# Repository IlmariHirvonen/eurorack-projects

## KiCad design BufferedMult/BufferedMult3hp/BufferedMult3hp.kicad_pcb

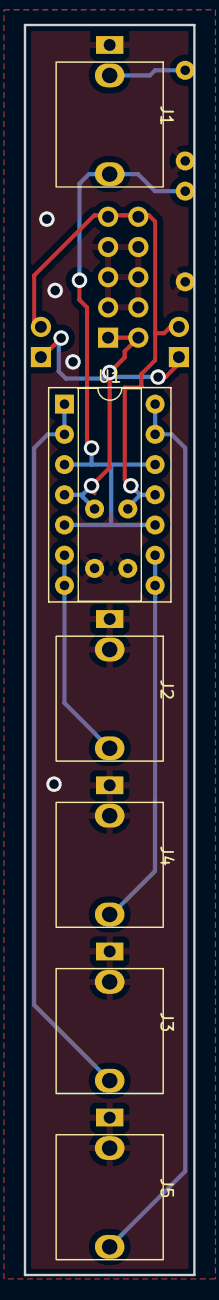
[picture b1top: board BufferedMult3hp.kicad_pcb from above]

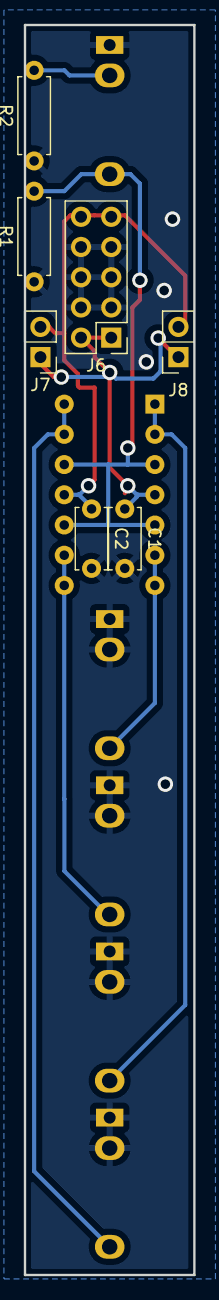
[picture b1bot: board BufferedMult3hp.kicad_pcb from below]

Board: 2 copper layers, 14.2 x 105.1 mm, 13 parts (7 on the bottom side), 9 nets.

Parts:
C1, C2: 100n; C_Disc_D5.0mm_W2.5mm_P5.00mm
J1, J2, J3, J4, J5: AudioJack2_SwitchT; Thonkiconn
J6: Conn_02x05_Odd_Even; PinHeader_2x05_P2.54mm_Vertical
J7: Conn_01x02_Male; PinHeader_1x02_P2.54mm_Vertical
J8: Conn_01x02_Female; PinSocket_1x02_P2.54mm_Vertical
R1: 1Meg; R_Axial_DIN0207_L6.3mm_D2.5mm_P7.62mm_Horizontal
R2: 20k; R_Axial_DIN0207_L6.3mm_D2.5mm_P7.62mm_Horizontal
U1: LM324; DIP-14_W7.62mm_Socket

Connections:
+12V: C1.1, J6.1, J6.2, J7.1, J8.1, U1.4 (V+)
-12V: C2.1, J6.9, J6.10, J7.2, J8.2, U1.11 (V-)
GND: C1.2, C2.2, J1.S, J2.S, J2.TN, J3.S, J3.TN, J4.S, J4.TN, J5.S, J5.TN, J6.3, J6.4, J6.5, J6.6, J6.7, J6.8, R1.1, R2.1
unnamed: J1.TN, R2.2
unnamed: J4.T, U1.8, U1.9 (-)
unnamed: J3.T, U1.1, U1.2 (-)
unnamed: J2.T, U1.6 (-), U1.7
unnamed: J1.T, R1.2, U1.3 (+), U1.5 (+), U1.10 (+), U1.12 (+)
unnamed: J5.T, U1.13 (-), U1.14

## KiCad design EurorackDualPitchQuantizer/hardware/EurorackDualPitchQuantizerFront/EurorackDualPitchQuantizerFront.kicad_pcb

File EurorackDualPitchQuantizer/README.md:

# EurorackDualPitchQuantizer
A simple Arduino and MCP4725 DAC based pitch quantizer. It might not be the best designed module or it might not work at all yet. I have yet to assemble a working unit or program the non test firmware for the microcontroller. I'll update this as the project goes along.

### Licenses
The license for hardware is under the hardware folder and for software under software folder. But in short:
Software: GPL3.0.
Hardware: CERN-OHL-S v2

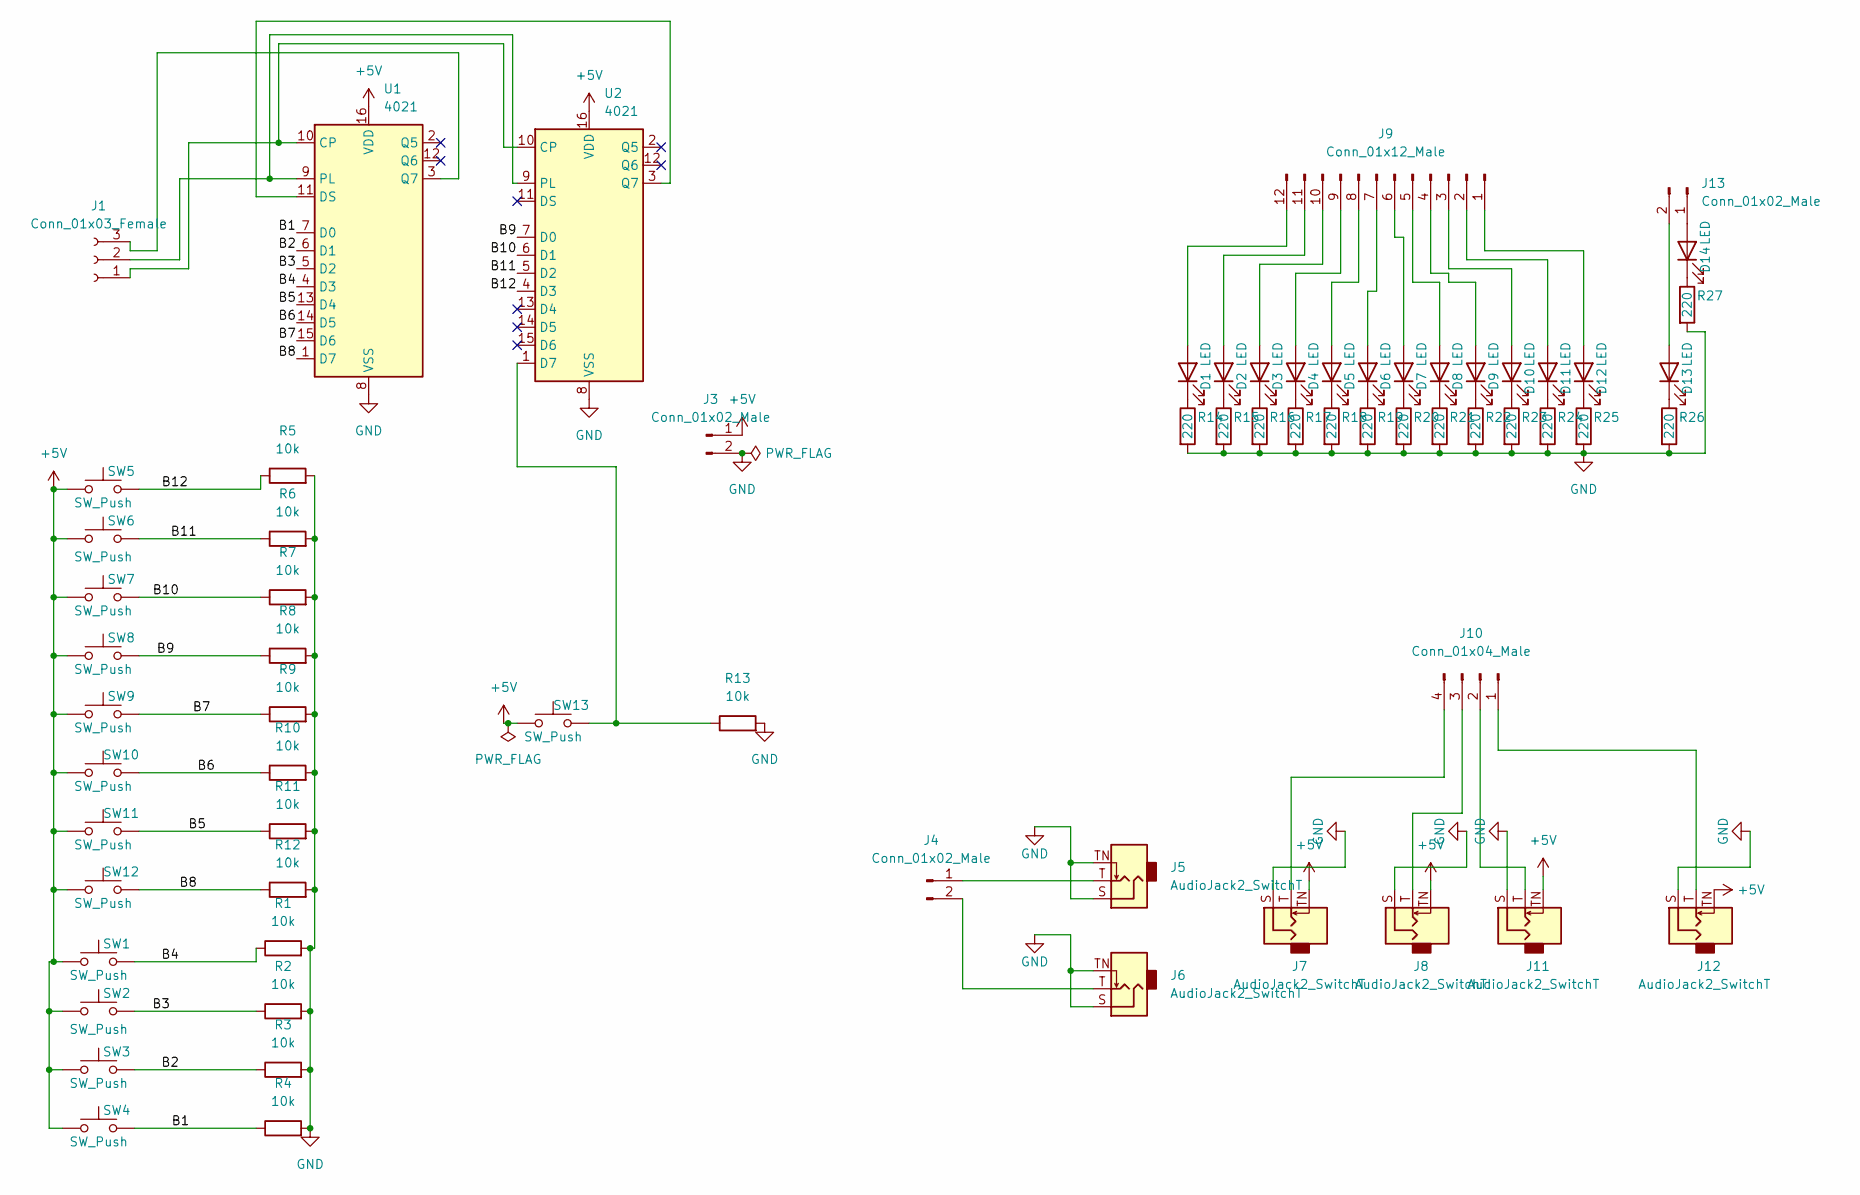
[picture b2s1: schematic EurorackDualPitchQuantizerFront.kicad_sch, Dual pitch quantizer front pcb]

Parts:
D1, D2, D3, D4, D5, D6, D7, D8, D9, D10, D11, D12, D13, D14: LED; LED_D3.0mm
J1: Conn_01x03_Female; PinHeader_1x03_P2.54mm_Vertical
J3, J4, J13: Conn_01x02_Male; PinHeader_1x02_P2.54mm_Vertical
J5, J6, J7, J8, J11, J12: AudioJack2_SwitchT; Thonkiconn
J9: Conn_01x12_Male; PinHeader_1x12_P2.54mm_Vertical
J10: Conn_01x04_Male; PinHeader_1x04_P2.54mm_Vertical
R1, R2, R3, R4, R5, R6, R7, R8, R9, R10, R11, R12, R13: 10k; R_Axial_DIN0207_L6.3mm_D2.5mm_P7.62mm_Horizontal
R14, R15, R16, R17, R18, R19, R20, R21, R22, R23, R24, R25, R26, R27: 220; R_Axial_DIN0207_L6.3mm_D2.5mm_P7.62mm_Horizontal
SW1, SW2, SW3, SW4, SW5, SW6, SW7, SW8, SW9, SW10, SW11, SW12, SW13: SW_Push; SW_PUSH_6mm
U1, U2: 4021; DIP-16_W7.62mm_Socket

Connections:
+5V: J3.1, J7.TN, J8.TN, J11.TN, J12.TN, SW1.1, SW2.1, SW3.1, SW4.1, SW5.1, SW6.1, SW7.1, SW8.1, SW9.1, SW10.1, SW11.1, SW12.1, SW13.1, U1.16 (VDD), U2.16 (VDD)
/B1: R4.1, SW4.2, U1.7 (D0)
/B2: R3.1, SW3.2, U1.6 (D1)
/B3: R2.1, SW2.2, U1.5 (D2)
/B4: R1.1, SW1.2, U1.4 (D3)
/B5: R11.1, SW11.2, U1.13 (D4)
/B6: R10.1, SW10.2, U1.14 (D5)
/B7: R9.1, SW9.2, U1.15 (D6)
/B8: R12.1, SW12.2, U1.1 (D7)
/B9: R8.1, SW8.2, U2.7 (D0)
/B10: R7.1, SW7.2, U2.6 (D1)
/B11: R6.1, SW6.2, U2.5 (D2)
/B12: R5.1, SW5.2, U2.4 (D3)
GND: J3.2, J5.S, J5.TN, J6.S, J6.TN, J7.S, J8.S, J11.S, J12.S, R1.2, R2.2, R3.2, R4.2, R5.2, R6.2, R7.2, R8.2, R9.2, R10.2, R11.2, R12.2, R13.2, R14.2, R15.2, R16.2, R17.2, R18.2, R19.2, R20.2, R21.2, R22.2, R23.2, R24.2, R25.2, R26.2, R27.2, U1.8 (VSS), U2.8 (VSS)
unnamed: D1.1 (K), R14.1
unnamed: D1.2 (A), J9.12
unnamed: D2.1 (K), R15.1
unnamed: D2.2 (A), J9.11
unnamed: D3.1 (K), R16.1
unnamed: D3.2 (A), J9.10
unnamed: D4.1 (K), R17.1
unnamed: D4.2 (A), J9.9
unnamed: D5.1 (K), R18.1
unnamed: D5.2 (A), J9.8
unnamed: D6.1 (K), R19.1
unnamed: D6.2 (A), J9.7
unnamed: D7.1 (K), R20.1
unnamed: D7.2 (A), J9.6
unnamed: D8.1 (K), R21.1
unnamed: D8.2 (A), J9.5
unnamed: D9.1 (K), R22.1
unnamed: D9.2 (A), J9.4
unnamed: D10.1 (K), R23.1
unnamed: D10.2 (A), J9.3
unnamed: D11.1 (K), R24.1
unnamed: D11.2 (A), J9.2
unnamed: D12.1 (K), R25.1
unnamed: D12.2 (A), J9.1
unnamed: D13.1 (K), R26.1
unnamed: D13.2 (A), J13.2
unnamed: D14.1 (K), R27.1
unnamed: D14.2 (A), J13.1
unnamed: J1.1, U1.10 (CP), U2.10 (CP)
unnamed: J1.2, U1.9 (PL), U2.9 (PL)
unnamed: J1.3, U1.3 (Q7)
unnamed: J4.1, J5.T
unnamed: J4.2, J6.T
unnamed: J10.1, J12.T
unnamed: J10.2, J11.T
unnamed: J8.T, J10.3
unnamed: J7.T, J10.4
unnamed: R13.1, SW13.2, U2.1 (D7)
unnamed: U1.11 (DS), U2.3 (Q7)

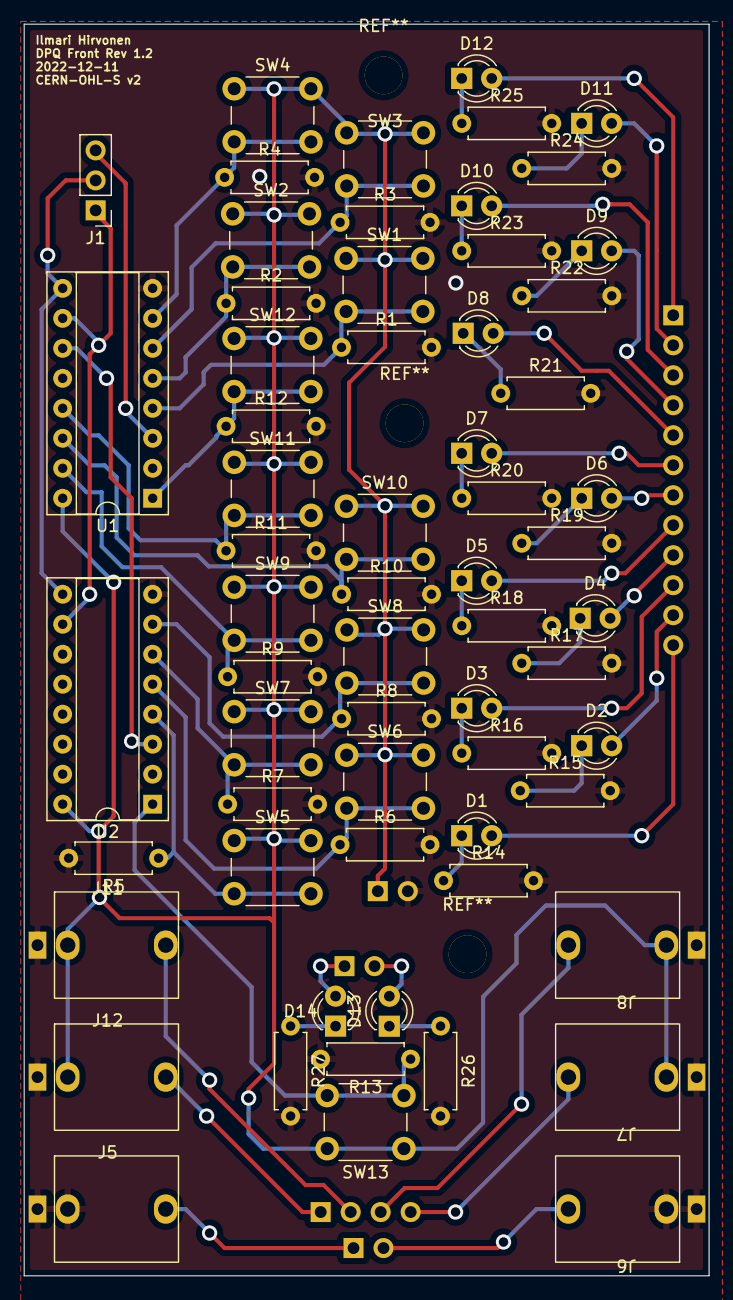
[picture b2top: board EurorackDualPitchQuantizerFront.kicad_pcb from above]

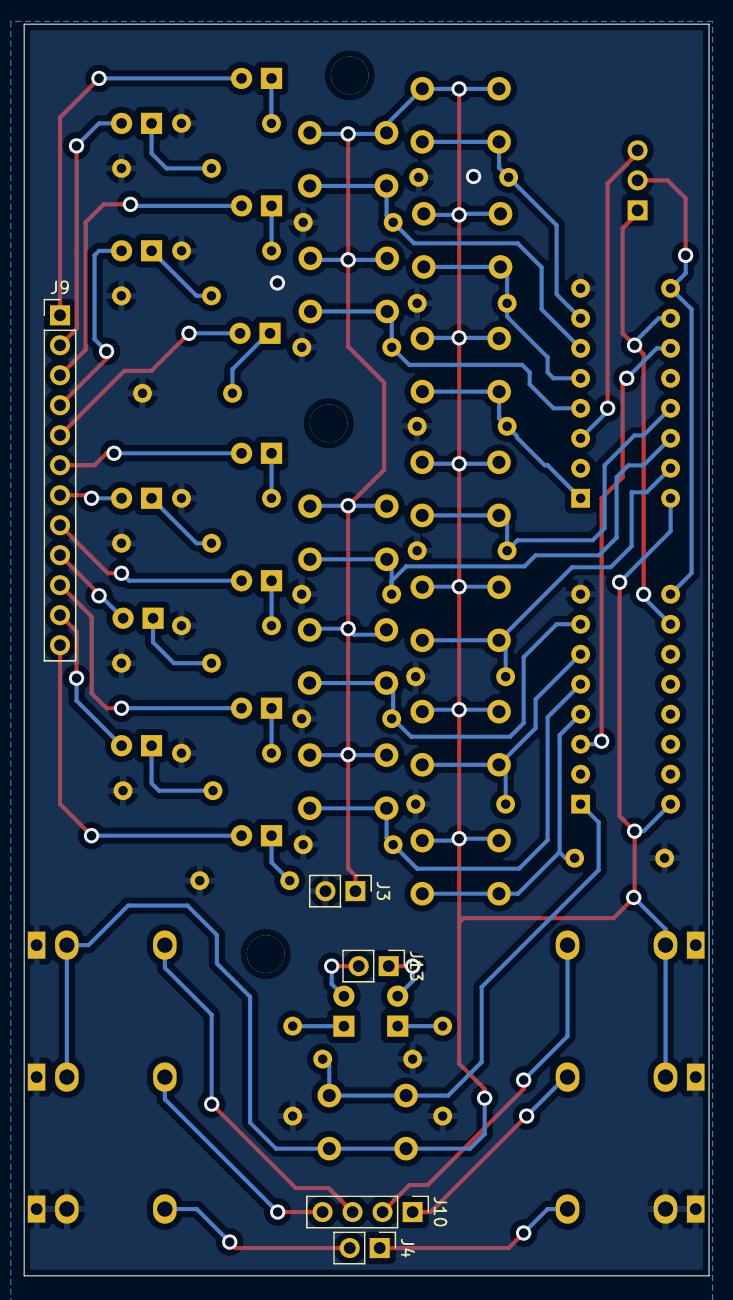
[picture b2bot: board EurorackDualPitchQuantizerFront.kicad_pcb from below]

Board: 2 copper layers, 58.0 x 106.0 mm, 68 parts (5 on the bottom side), 53 nets.

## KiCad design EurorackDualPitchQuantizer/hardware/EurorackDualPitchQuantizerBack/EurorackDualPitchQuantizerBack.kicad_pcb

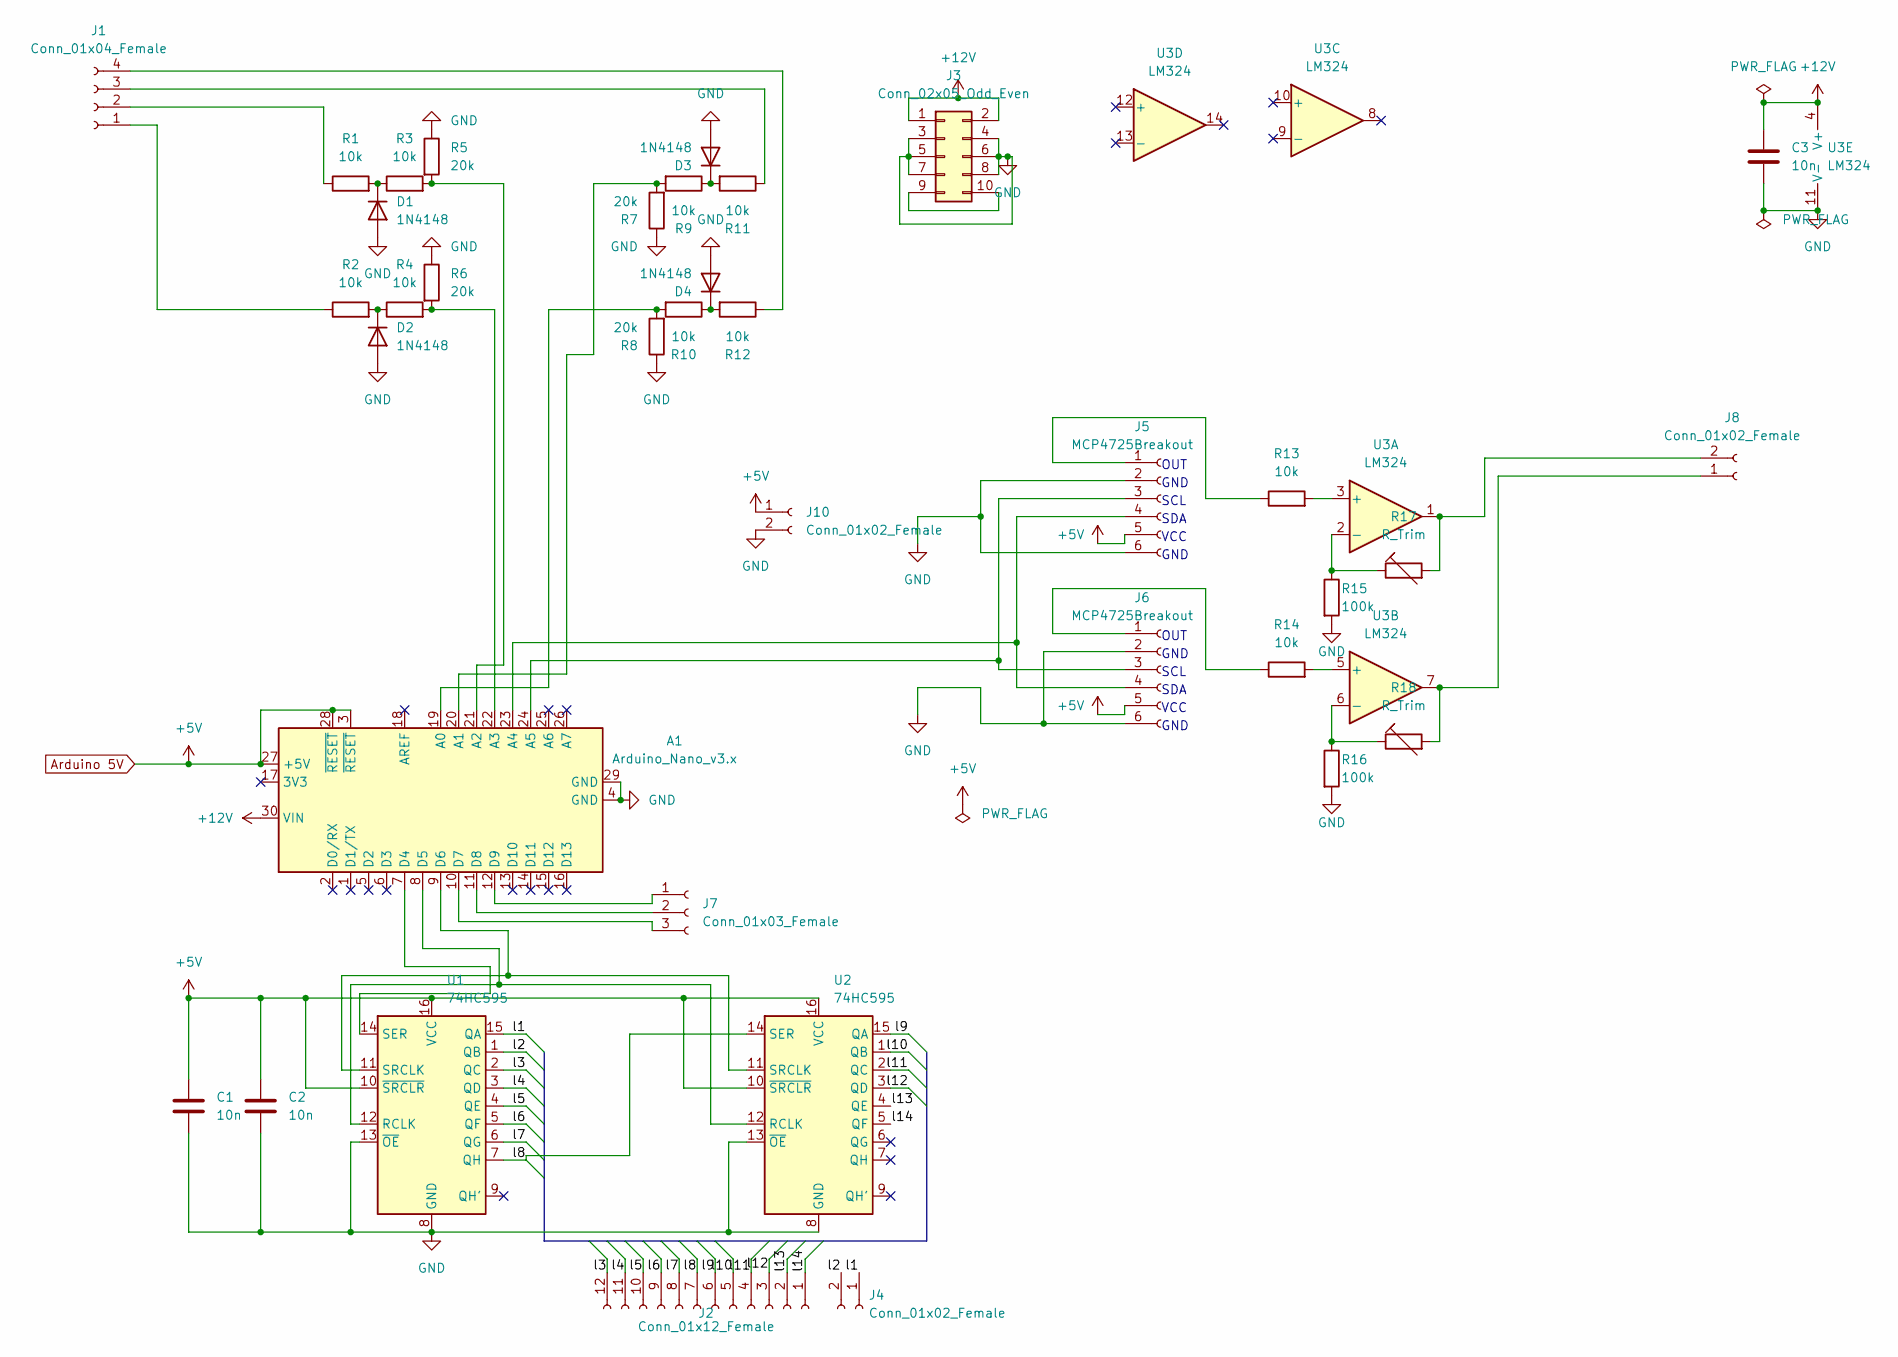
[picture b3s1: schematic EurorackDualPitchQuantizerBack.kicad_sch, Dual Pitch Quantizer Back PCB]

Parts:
A1: Arduino_Nano_v3.x; Arduino_Nano
C1, C2, C3: 10n; C_Disc_D3.0mm_W2.0mm_P2.50mm
D1, D2, D3, D4: 1N4148; D_DO-35_SOD27_P7.62mm_Horizontal
J1: Conn_01x04_Female; PinSocket_1x04_P2.54mm_Vertical
J2: Conn_01x12_Female; PinSocket_1x12_P2.54mm_Vertical
J3: Conn_02x05_Odd_Even; PinHeader_2x05_P2.54mm_Vertical
J4, J8: Conn_01x02_Female; PinSocket_1x02_P2.54mm_Vertical
J5, J6: MCP4725Breakout; PinSocket_1x06_P2.54mm_Vertical
J7: Conn_01x03_Female; PinHeader_1x03_P2.54mm_Vertical
J10: Conn_01x02_Female; PinHeader_1x02_P2.54mm_Vertical
R1, R2, R3, R4, R9, R10, R11, R12, R13, R14: 10k; R_Axial_DIN0207_L6.3mm_D2.5mm_P7.62mm_Horizontal
R5, R6, R7, R8: 20k; R_Axial_DIN0207_L6.3mm_D2.5mm_P7.62mm_Horizontal
R15, R16: 100k; R_Axial_DIN0207_L6.3mm_D2.5mm_P7.62mm_Horizontal
R17, R18: R_Trim; PinHeader_1x03_P2.54mm_Vertical
U1, U2: 74HC595; DIP-16_W7.62mm_Socket
U3: LM324; DIP-14_W7.62mm_Socket

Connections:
+12V: A1.30 (VIN), C3.1, J3.1, J3.2, U3.4 (V+)
/l1: J4.1, U1.15 (QA)
/l2: J4.2, U1.1 (QB)
/l3: J2.12, U1.2 (QC)
/l4: J2.11, U1.3 (QD)
/l5: J2.10, U1.4 (QE)
/l6: J2.9, U1.5 (QF)
/l7: J2.8, U1.6 (QG)
/l8: J2.7, U1.7 (QH), U2.14 (SER)
/l9: J2.6, U2.15 (QA)
/l10: J2.5, U2.1 (QB)
/l11: J2.4, U2.2 (QC)
/l12: J2.3, U2.3 (QD)
/l13: J2.2, U2.4 (QE)
/l14: J2.1, U2.5 (QF)
Arduino 5V: A1.3 (~RESET), A1.27 (+5V), A1.28 (~RESET), C1.1, C2.1, J5.5, J6.5, J10.1, U1.10 (~SRCLR), U1.16 (VCC), U2.10 (~SRCLR), U2.16 (VCC)
GND: A1.4 (GND), A1.29 (GND), C1.2, C2.2, C3.2, D1.2 (A), D2.2 (A), D3.2 (A), D4.2 (A), J3.3, J3.4, J3.5, J3.6, J3.7, J3.8, J5.2, J5.6, J6.2, J6.6, J10.2, R5.1, R6.1, R7.1, R8.1, R15.2, R16.2, U1.8 (GND), U1.13 (~OE), U2.8 (GND), U2.13 (~OE), U3.11 (V-)
unnamed: A1.7 (D4), U1.14 (SER)
unnamed: A1.8 (D5), U1.12 (RCLK), U2.12 (RCLK)
unnamed: A1.9 (D6), U1.11 (SRCLK), U2.11 (SRCLK)
unnamed: A1.10 (D7), J7.3
unnamed: A1.11 (D8), J7.2
unnamed: A1.12 (D9), J7.1
unnamed: A1.19 (A0), R8.2, R10.2
unnamed: A1.20 (A1), R7.2, R9.2
unnamed: A1.21 (A2), R3.2, R5.2
unnamed: A1.22 (A3), R4.2, R6.2
unnamed: A1.23 (A4), J5.4, J6.4
unnamed: A1.24 (A5), J5.3, J6.3
unnamed: D1.1 (K), R1.2, R3.1
unnamed: D2.1 (K), R2.2, R4.1
unnamed: D3.1 (K), R9.1, R11.2
unnamed: D4.1 (K), R10.1, R12.2
unnamed: J1.1, R2.1
unnamed: J1.2, R1.1
unnamed: J1.3, R11.1
unnamed: J1.4, R12.1
unnamed: J3.9, J3.10
unnamed: J5.1, R13.1
unnamed: J6.1, R14.1
unnamed: J8.2, R17.2, U3.1
unnamed: R13.2, U3.3 (+)
unnamed: R14.2, U3.5 (+)
unnamed: R15.1, R17.1, U3.2 (-)
unnamed: R16.1, R18.1, U3.6 (-)
unnamed: J8.1, R18.2, U3.7

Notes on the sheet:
GND
SDA
SCL
OUT
VCC

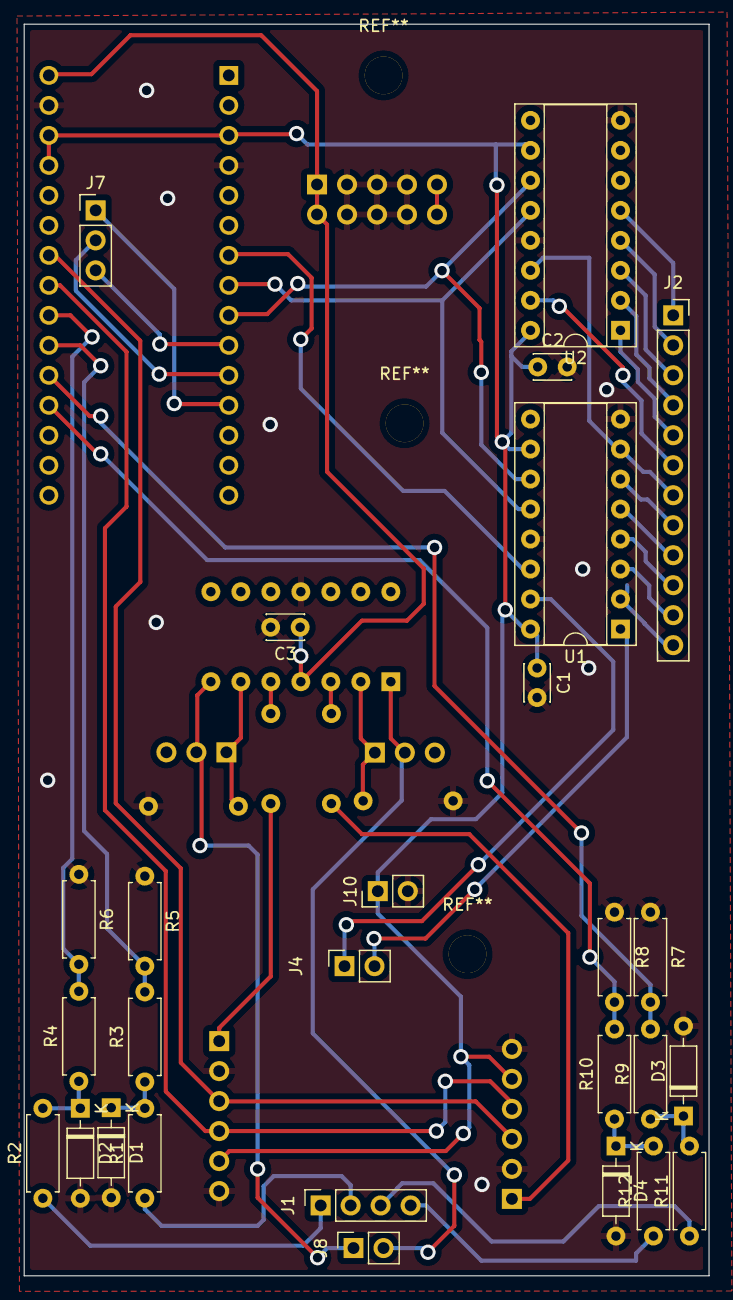
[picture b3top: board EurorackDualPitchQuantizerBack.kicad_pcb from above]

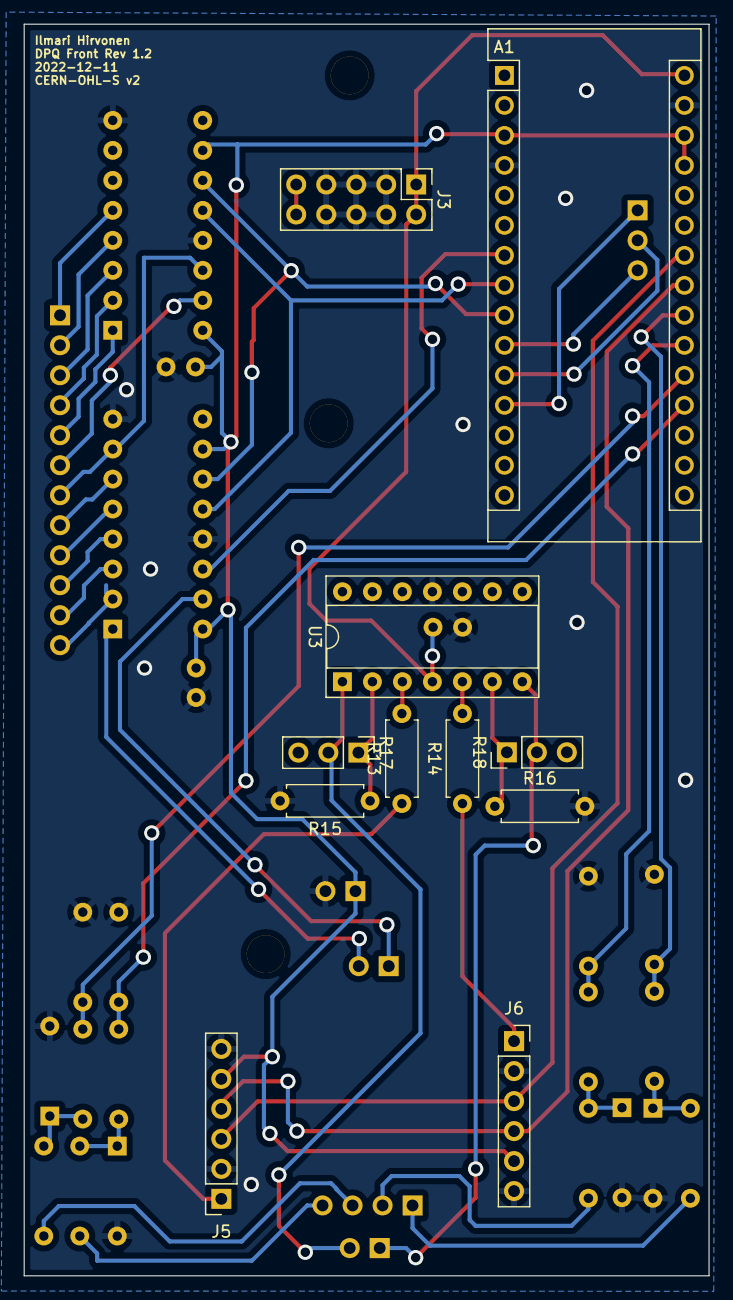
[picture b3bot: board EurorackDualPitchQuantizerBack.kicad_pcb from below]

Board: 2 copper layers, 58.0 x 106.0 mm, 38 parts (11 on the bottom side), 46 nets.

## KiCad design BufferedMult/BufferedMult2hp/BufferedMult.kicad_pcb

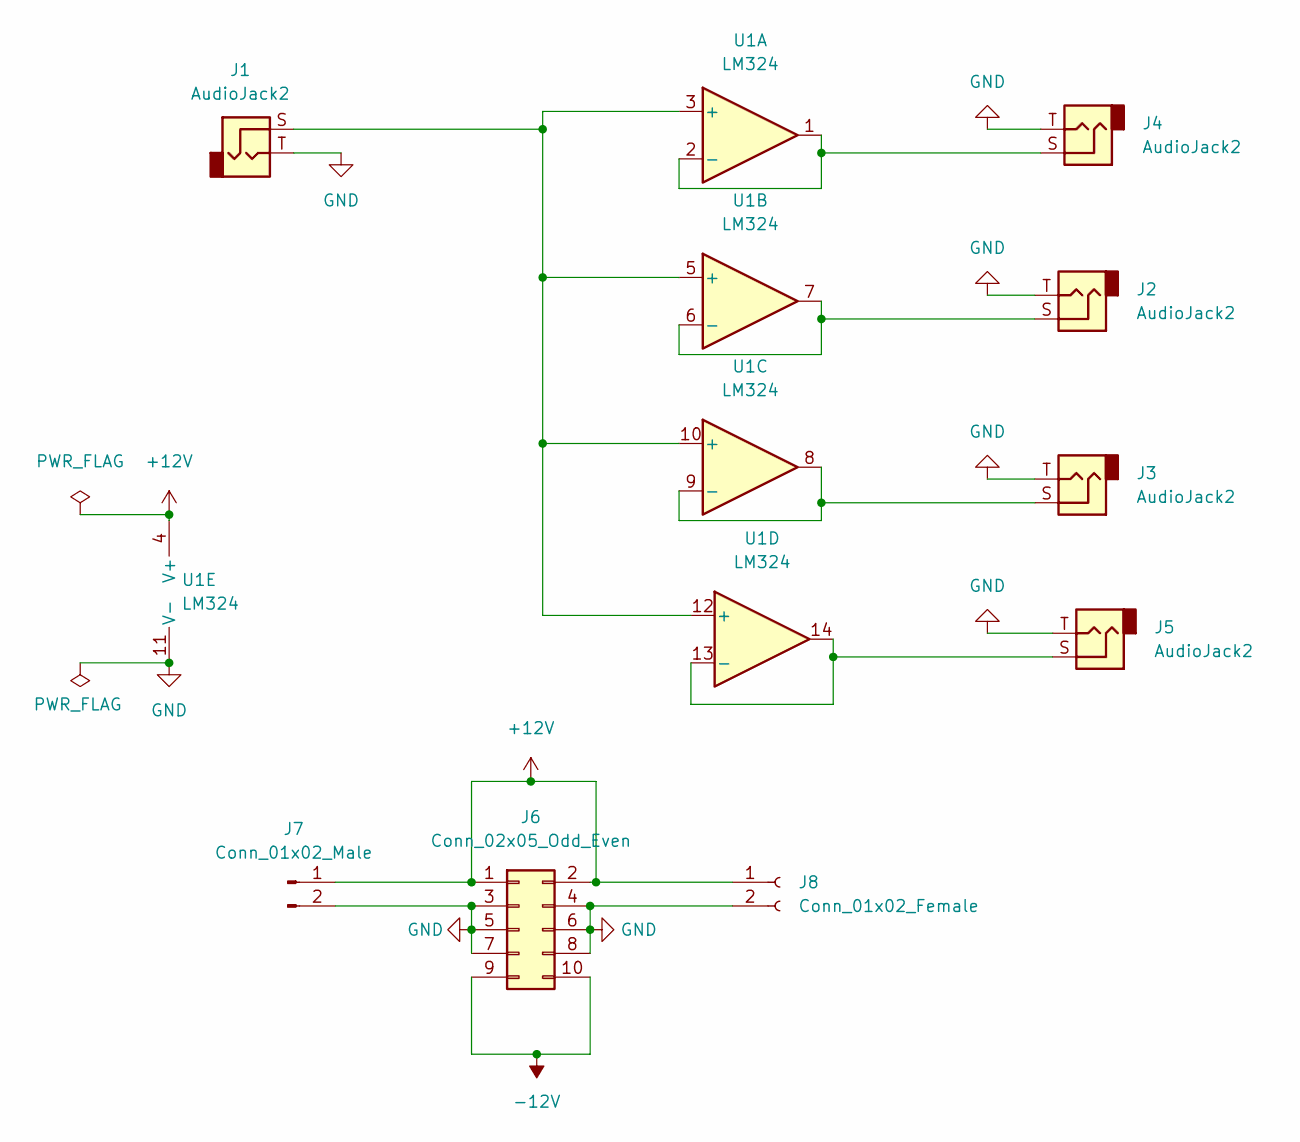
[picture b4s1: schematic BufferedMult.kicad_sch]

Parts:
J1, J2, J3, J4, J5: AudioJack2; Thonkiconn
J6: Conn_02x05_Odd_Even; PinHeader_2x05_P2.54mm_Vertical
J7: Conn_01x02_Male; PinHeader_1x02_P2.54mm_Vertical
J8: Conn_01x02_Female; PinSocket_1x02_P2.54mm_Vertical
U1: LM324; DIP-14_W7.62mm_Socket

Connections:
+12V: J6.1, J6.2, J7.1, J8.1, U1.4 (V+)
-12V: J6.9, J6.10
GND: J1.T, J2.T, J3.T, J4.T, J5.T, J6.3, J6.4, J6.5, J6.6, J6.7, J6.8, J7.2, J8.2, U1.11 (V-)
unnamed: J1.S, U1.3 (+), U1.5 (+), U1.10 (+), U1.12 (+)
unnamed: J2.S, U1.6 (-), U1.7
unnamed: J3.S, U1.8, U1.9 (-)
unnamed: J4.S, U1.1, U1.2 (-)
unnamed: J5.S, U1.13 (-), U1.14

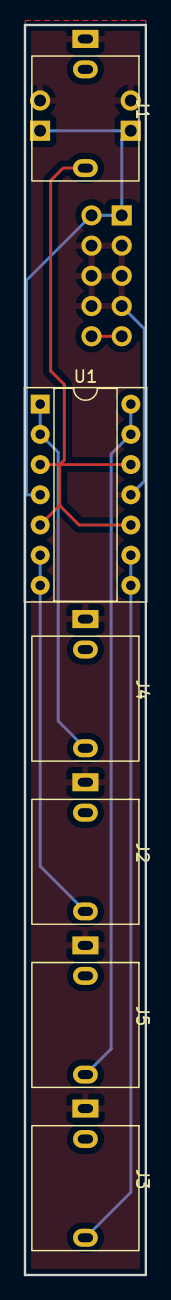
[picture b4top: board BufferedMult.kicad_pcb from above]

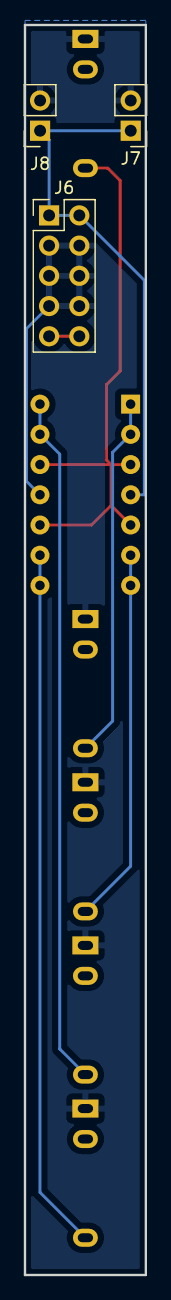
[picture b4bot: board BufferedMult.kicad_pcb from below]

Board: 2 copper layers, 10.2 x 105.1 mm, 9 parts (3 on the bottom side), 8 nets.

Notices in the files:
EurorackDualPitchQuantizer/hardware/EurorackDualPitchQuantizerBack/EurorackDualPitchQuantizerBack.kicad_sch:
License: CERN-OHL-S v2
